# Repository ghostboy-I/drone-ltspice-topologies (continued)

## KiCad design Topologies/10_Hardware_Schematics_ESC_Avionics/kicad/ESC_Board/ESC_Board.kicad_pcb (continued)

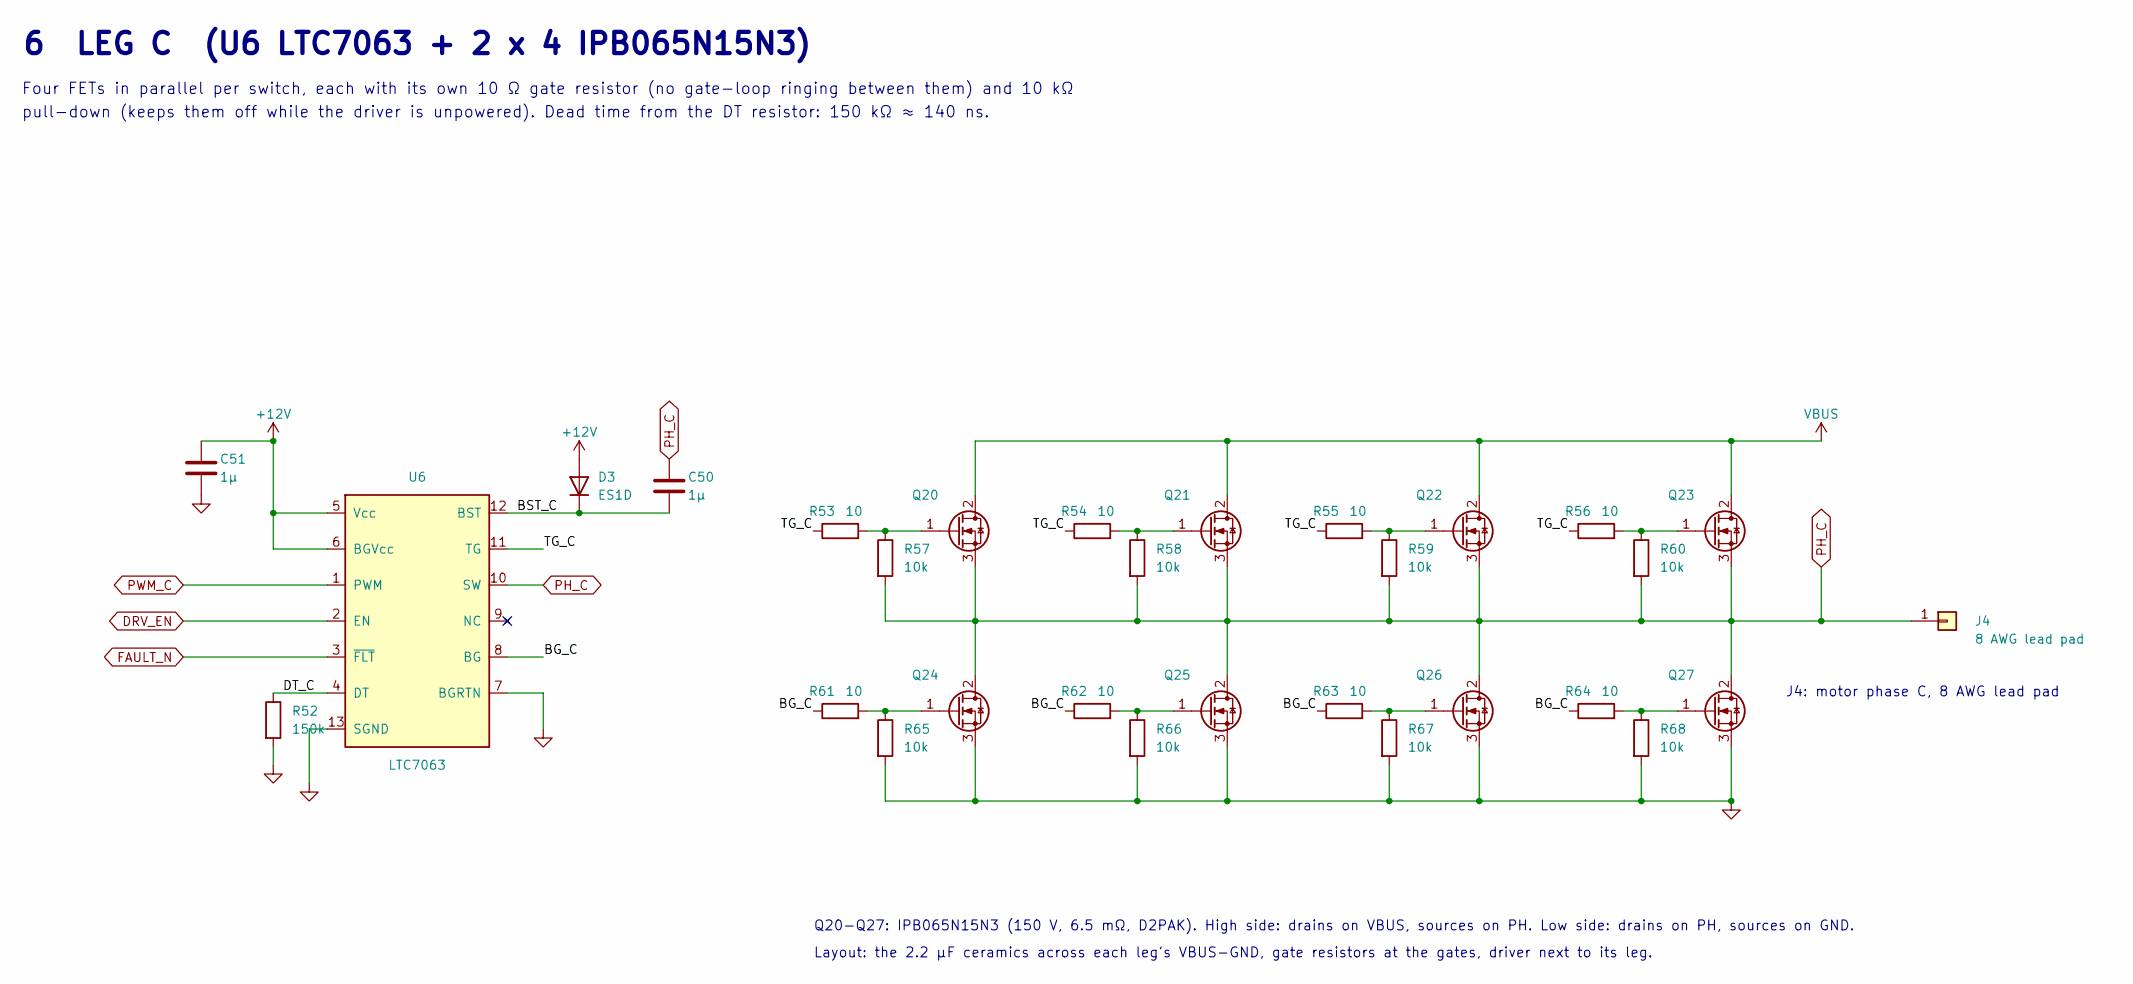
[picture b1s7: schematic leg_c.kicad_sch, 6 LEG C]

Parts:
C50, C51: 1µ; C_0805_2012Metric; Rating 25 V; MPN/Spec X7R
D3: ES1D; D_SMA; Rating 200 V 1 A; MPN/Spec ES1D
J4: 8 AWG lead pad; SolderWire-8AWG_1x01_D4.2mm_OD7mm; MPN/Spec 8 AWG lead pad (8 mm bullet on the lead)
Q20, Q21, Q22, Q23, Q24, Q25, Q26, Q27: IPB065N15N3; TO-263-2; Rating 150 V 130 A; MPN/Spec Infineon IPB065N15N3 G
R52: 150k; R_0603_1608Metric; MPN/Spec 1 %, thick film
R53, R54, R55, R56, R61, R62, R63, R64: 10; R_0603_1608Metric; MPN/Spec 1 %
R57, R58, R59, R60, R65, R66, R67, R68: 10k; R_0603_1608Metric; MPN/Spec 1 %
U6: LTC7063; MSOP-12-1EP_3x4.039mm_P0.65mm_EP1.651x2.845mm; Rating 150 V; MPN/Spec LTC7063EMSE (MSOP-12)

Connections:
+12V: C51.1, D3.2 (A), U6.5 (Vcc), U6.6 (BGVcc); also elsewhere on the board
/Leg_C/BG_C: R61.1, R62.1, R63.1, R64.1, U6.8 (BG)
/Leg_C/BST_C: C50.1, D3.1 (K), U6.12 (BST)
/Leg_C/DT_C: R52.1, U6.4 (DT)
/Leg_C/TG_C: R53.1, R54.1, R55.1, R56.1, U6.11 (TG)
DRV_EN: U6.2 (EN); also elsewhere on the board
FAULT_N: U6.3 (~FLT); also elsewhere on the board
GND: C51.2, Q24.3 (S), Q25.3 (S), Q26.3 (S), Q27.3 (S), R52.2, R65.2, R66.2, R67.2, R68.2, U6.7 (BGRTN), U6.13 (SGND); also elsewhere on the board
unnamed: Q20.1 (G), R53.2, R57.1
unnamed: Q21.1 (G), R54.2, R58.1
unnamed: Q22.1 (G), R55.2, R59.1
unnamed: Q23.1 (G), R56.2, R60.1
unnamed: Q24.1 (G), R61.2, R65.1
unnamed: Q25.1 (G), R62.2, R66.1
unnamed: Q26.1 (G), R63.2, R67.1
unnamed: Q27.1 (G), R64.2, R68.1
PH_C: C50.2, J4.1, Q20.3 (S), Q21.3 (S), Q22.3 (S), Q23.3 (S), Q24.2 (D), Q25.2 (D), Q26.2 (D), Q27.2 (D), R57.2, R58.2, R59.2, R60.2, U6.10 (SW)
PWM_C: U6.1 (PWM); also elsewhere on the board
VBUS: Q20.2 (D), Q21.2 (D), Q22.2 (D), Q23.2 (D); also elsewhere on the board

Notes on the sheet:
6 LEG C (U6 LTC7063 + 2 x 4 IPB065N15N3)
Four FETs in parallel per switch, each with its own 10 Ω gate resistor (no gate-loop ringing between them) and 10 kΩ
pull-down (keeps them off while the driver is unpowered). Dead time from the DT resistor: 150 kΩ ≈ 140 ns.
J4: motor phase C, 8 AWG lead pad
Q20-Q27: IPB065N15N3 (150 V, 6.5 mΩ, D2PAK). High side: drains on VBUS, sources on PH. Low side: drains on PH, sources on GND.
Layout: the 2.2 µF ceramics across each leg's VBUS-GND, gate resistors at the gates, driver next to its leg.

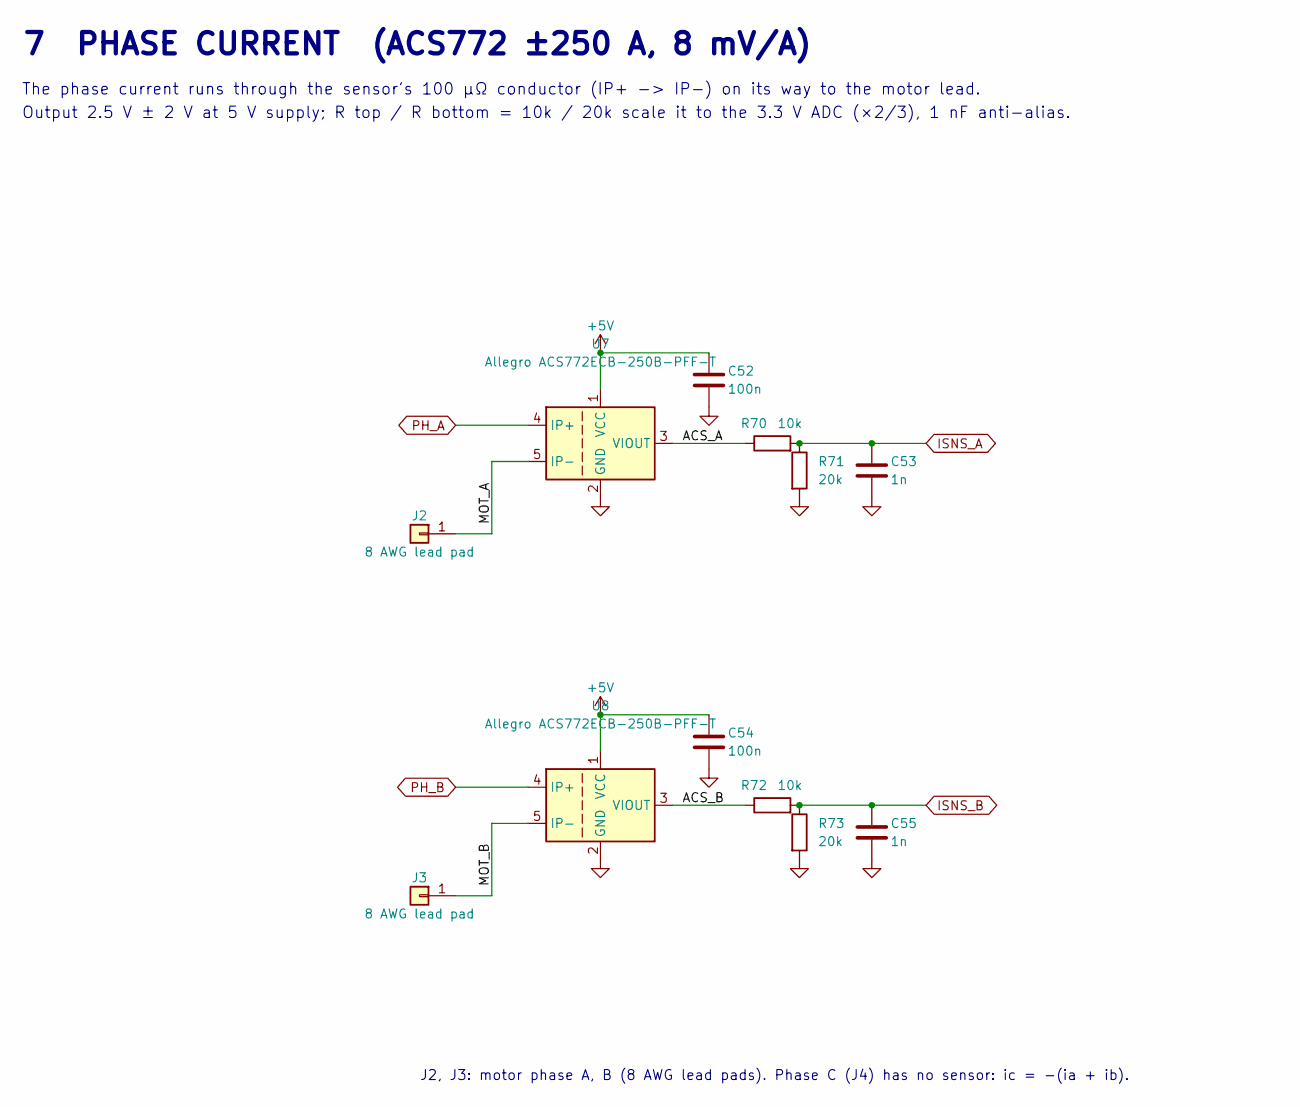
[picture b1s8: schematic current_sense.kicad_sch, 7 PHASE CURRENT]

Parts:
C52, C54: 100n; C_0603_1608Metric; MPN/Spec X7R
C53, C55: 1n; C_0603_1608Metric; MPN/Spec X7R
J2, J3: 8 AWG lead pad; SolderWire-8AWG_1x01_D4.2mm_OD7mm; MPN/Spec 8 AWG lead pad (8 mm bullet on the lead)
R70, R72: 10k; R_0603_1608Metric; MPN/Spec 1 %, thick film
R71, R73: 20k; R_0603_1608Metric; MPN/Spec 1 %, thick film
U7, U8: Allegro ACS772ECB-250B-PFF-T; Allegro_CB_PFF; Rating ±250 A; MPN/Spec Allegro ACS772ECB-250B-PFF-T

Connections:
+5V: C52.1, C54.1, U7.1 (VCC), U8.1 (VCC); also elsewhere on the board
/Current_Sense/ACS_A: R70.1, U7.3 (VIOUT)
/Current_Sense/ACS_B: R72.1, U8.3 (VIOUT)
/Current_Sense/MOT_A: J2.1, U7.5 (IP-)
/Current_Sense/MOT_B: J3.1, U8.5 (IP-)
GND: C52.2, C53.2, C54.2, C55.2, R71.2, R73.2, U7.2 (GND), U8.2 (GND); also elsewhere on the board
ISNS_A: C53.1, R70.2, R71.1; also elsewhere on the board
ISNS_B: C55.1, R72.2, R73.1; also elsewhere on the board
PH_A: U7.4 (IP+); also elsewhere on the board
PH_B: U8.4 (IP+); also elsewhere on the board

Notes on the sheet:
7 PHASE CURRENT (ACS772 ±250 A, 8 mV/A)
The phase current runs through the sensor's 100 µΩ conductor (IP+ -> IP-) on its way to the motor lead.
Output 2.5 V ± 2 V at 5 V supply; R top / R bottom = 10k / 20k scale it to the 3.3 V ADC (×2/3), 1 nF anti-alias.
J2, J3: motor phase A, B (8 AWG lead pads). Phase C (J4) has no sensor: ic = -(ia + ib).

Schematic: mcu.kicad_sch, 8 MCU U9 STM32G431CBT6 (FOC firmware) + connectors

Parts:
C56, C57, C58, C59, C62, C63: 100n; C_0603_1608Metric; MPN/Spec X7R
C60: 4.7µ; C_0805_2012Metric; Rating 10 V; MPN/Spec X7R
C61: 1µ; C_0603_1608Metric; MPN/Spec X7R
D4: QTLP690C; LED_0603_1608Metric; MPN/Spec any 0603 green LED
FB1: 600R@100MHz; L_0603_1608Metric; MPN/Spec Murata BLM18PG601SN1
J5: GH 3 pin; JST_GH_BM03B-GHS-TBT_1x03-1MP_P1.25mm_Vertical; MPN/Spec JST GH 3 pin
J6: GH 6 pin; JST_GH_BM06B-GHS-TBT_1x06-1MP_P1.25mm_Vertical; MPN/Spec JST GH 6 pin
J7: Tag-Connect TC2030-NL; Tag-Connect_TC2030-IDC-NL_2x03_P1.27mm_Vertical; MPN/Spec Tag-Connect TC2030-NL
R69, R74: 10k; R_0603_1608Metric; MPN/Spec 1 %, thick film
R75: 1k; R_0603_1608Metric; MPN/Spec 1 %, thick film
R76: 100; R_0603_1608Metric; MPN/Spec 1 %, thick film
U9: ST STM32G431CBT6; LQFP-48_7x7mm_P0.5mm; MPN/Spec ST STM32G431CBT6 (LQFP-48)

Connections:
+3V3: C56.1, C57.1, C58.1, C59.1, C60.1, D4.2 (A), FB1.1, J7.1, R69.1, U9.1 (VBAT), U9.24 (VDD), U9.36 (VDD), U9.48 (VDD); also elsewhere on the board
+5V: J6.1; also elsewhere on the board
/MCU/BOOT0: R74.1, U9.45 (PB8)
/MCU/ENC_CS: J6.3, U9.12 (PA4)
/MCU/ENC_MISO: J6.5, U9.14 (PA6)
/MCU/ENC_MOSI: J6.6, U9.15 (PA7)
/MCU/ENC_SCK: J6.4, U9.13 (PA5)
/MCU/LED: R75.1, U9.2 (PC13)
/MCU/NRST: C63.1, J7.3, U9.7 (PG10)
/MCU/SIG_IN: R76.2, U9.39 (PA15)
/MCU/SWCLK: J7.4, U9.38 (PA14)
/MCU/SWDIO: J7.2, U9.37 (PA13)
/MCU/TLM_TX: J5.2, U9.43 (PB6)
DRV_EN: U9.16 (PB0); also elsewhere on the board
FAULT_N: R69.2, U9.26 (PB12); also elsewhere on the board
GND: C56.2, C57.2, C58.2, C59.2, C60.2, C61.2, C62.2, C63.2, J5.3, J6.2, J7.5, R74.2, U9.19 (VSSA), U9.23 (VSS), U9.35 (VSS), U9.47 (VSS); also elsewhere on the board
ISNS_A: U9.8 (PA0); also elsewhere on the board
ISNS_B: U9.9 (PA1); also elsewhere on the board
unnamed: D4.1 (K), R75.2
unnamed: J5.1, R76.1
PWM_A: U9.30 (PA8); also elsewhere on the board
PWM_B: U9.31 (PA9); also elsewhere on the board
PWM_C: U9.32 (PA10); also elsewhere on the board
TEMP: U9.11 (PA3); also elsewhere on the board
VBUS_SNS: U9.10 (PA2); also elsewhere on the board
VDDA: C61.1, C62.1, FB1.2, U9.20 (VREF+), U9.21 (VDDA)

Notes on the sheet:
8 MCU (U9 STM32G431CBT6, Cortex-M4F 170 MHz)
TIM1 CH1-3 (PA8-PA10) drive the three legs; ADC on PA0-PA3; SPI1 (PA4-PA7) reads the AS5047P encoder;
PA15 takes DShot from the flight controller, PB6 sends telemetry. The pin map is a proposal: check it in STM32CubeMX.
C56-C59 100 nF at the four VDD/VBAT pins, C60 4.7 µF
VDDA / VREF+: ferrite bead + 1 µF + 100 nF
R69: pull-up for the three drivers' open-drain FLT outputs (wired-OR)
J5: DShot in (R76 100 Ω series), telemetry out, GND (JST GH 3)
J6: AS5047P encoder on the motor, SPI (JST GH 6)
J7: Tag-Connect TC2030-NL (SWD); pad 6 SWO unused

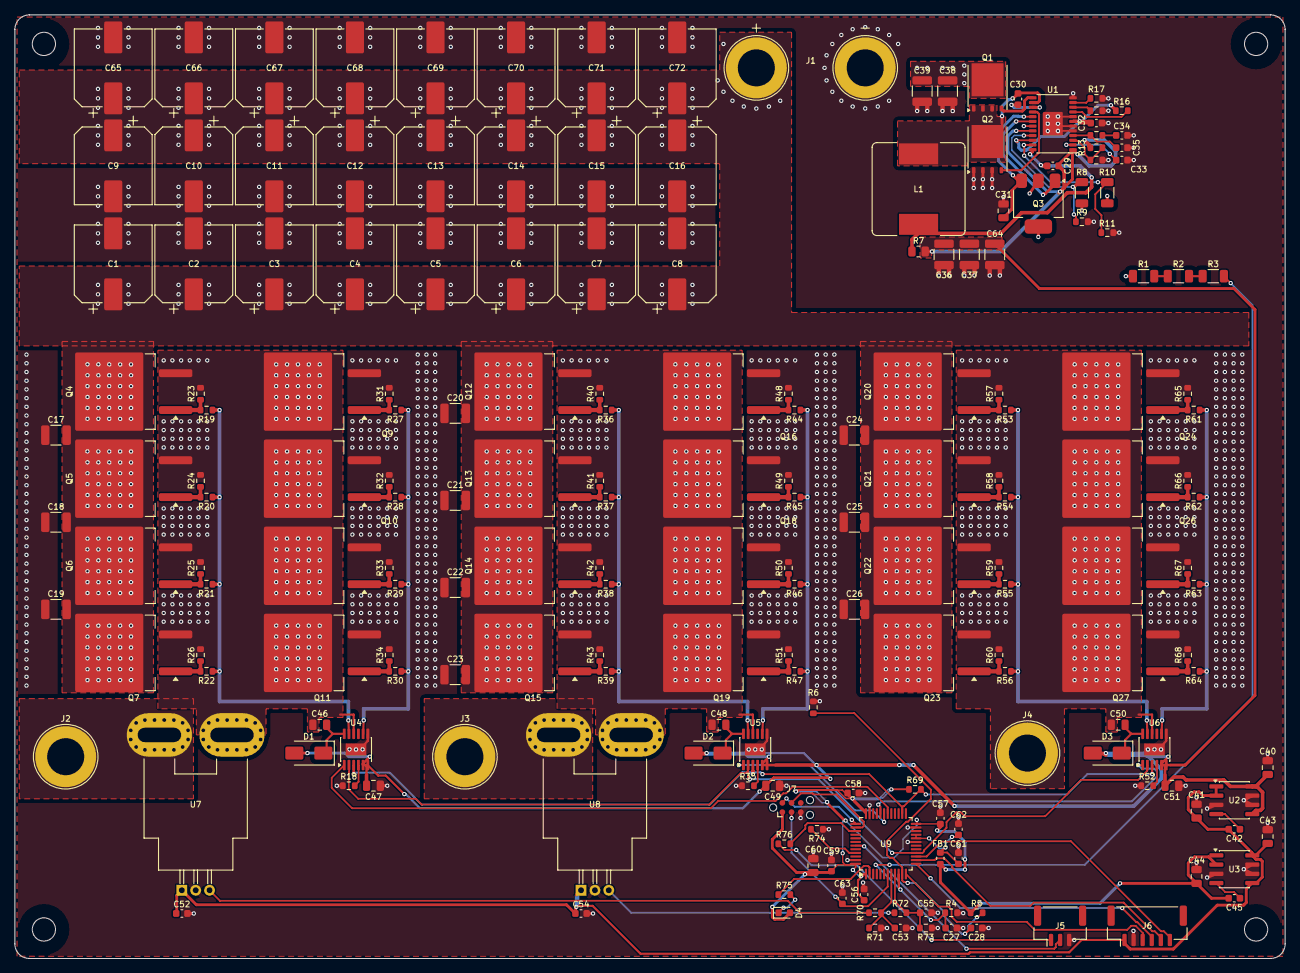
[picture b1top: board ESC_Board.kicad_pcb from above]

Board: 4 copper layers, 175.0 x 130.0 mm, 201 parts (0 on the bottom side), 92 nets.

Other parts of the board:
H1, H2, H3, H4: M3; MountingHole_3.2mm_M3

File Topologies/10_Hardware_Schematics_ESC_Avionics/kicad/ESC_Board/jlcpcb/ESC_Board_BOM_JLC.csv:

Comment,Designator,Footprint,LCSC Part #
"150u 150 uF 125 V hybrid polymer, >=3.5 A ripple, ESR <= 20 mR 125 V","C1,C2,C3,C4,C5,C6,C7,C8,C9,C10,C11,C12,C13,C14,C15,C16,C65,C66,C67,C68,C69,C70,C71,C72",CP_Elec_10x12.5,
2.2u 2.2 uF X7R 1210 (~1.1 uF at 90 V) 250 V,"C17,C18,C19,C20,C21,C22,C23,C24,C25,C26,C38,C39",C_1210_3225Metric,
10n X7R,"C27,C33",C_0603_1608Metric,
100n X7R,"C28,C52,C54,C56,C57,C58,C59,C62,C63",C_0603_1608Metric,
1n X7R,"C29,C53,C55",C_0603_1608Metric,
0.1u X7R 25 V,C30,C_0603_1608Metric,
4.7u X7R 25 V,C31,C_0805_2012Metric,
0.1u X7R,C32,C_0603_1608Metric,
1.8n X7R,C34,C_0603_1608Metric,
18p X7R,C35,C_0603_1608Metric,
10u 10 uF X7R 1210 (5 uF at 12 V) 25 V,"C36,C37",C_1210_3225Metric,
1u X7R 25 V,"C40,C46,C47,C48,C49,C50,C51",C_0805_2012Metric,
10u X7R 10 V,"C41,C44",C_0805_2012Metric,
"10 nF X7R 10 nF X7R, DNP","C42,C45",C_0603_1608Metric,
1u X7R 10 V,C43,C_0805_2012Metric,
4.7u X7R 10 V,C60,C_0805_2012Metric,
1u X7R,C61,C_0603_1608Metric,
47u 47 uF X7R 1210 (~22 uF at 12 V) 25 V,C64,C_1210_3225Metric,
ES1D ES1D 200 V 1 A,"D1,D2,D3",D_SMA,
QTLP690C any 0603 green LED,D4,LED_0603_1608Metric,
600R@100MHz Murata BLM18PG601SN1,FB1,L_0603_1608Metric,
"AS150 with factory 8 AWG pigtail AMASS AS150 with factory 8 AWG pigtail (male) 150 A, 24S",J1,AMASS_AS150_Pigtail_2x8AWG_P15mm,
8 AWG lead pad 8 AWG lead pad (8 mm bullet on the lead),"J2,J3,J4",SolderWire-8AWG_1x01_D4.2mm_OD7mm,
GH 3 pin JST GH 3 pin,J5,JST_GH_BM03B-GHS-TBT_1x03-1MP_P1.25mm_Vertical,
GH 6 pin JST GH 6 pin,J6,JST_GH_BM06B-GHS-TBT_1x06-1MP_P1.25mm_Vertical,
Tag-Connect TC2030-NL Tag-Connect TC2030-NL,J7,Tag-Connect_TC2030-IDC-NL_2x03_P1.27mm_Vertical,
"150u shielded, Isat >= 1 A, DCR <= 0.4 R Isat 1 A",L1,L_Bourns_SRR1260,
BSC520N15NS3 Infineon BSC520N15NS3 150 V 21 A,Q1,TDSON-8-1,
BSC360N15NS3 Infineon BSC360N15NS3 150 V 30 A,Q2,TDSON-8-1,
BSP89 Infineon BSP89 240 V,Q3,SOT-223-3_TabPin2,
IPB065N15N3 Infineon IPB065N15N3 G 150 V 130 A,"Q4,Q5,Q6,Q7,Q8,Q9,Q10,Q11,Q12,Q13,Q14,Q15,Q16,Q17,Q18,Q19,Q20,Q21,Q22,Q23,Q24,Q25,Q26,Q27",TO-263-2,
"330k 1 %, thick film 200 V","R1,R2,R3",R_1206_3216Metric,
"33k 1 %, thick film",R4,R_0603_1608Metric,
"10k 1 %, thick film","R5,R14,R69,R70,R72,R74",R_0603_1608Metric,
10k NTC 10 kR B3950,R6,R_0603_1608Metric,
100m current sense 1 % 0.25 W,R7,R_0805_2012Metric,
"976k 1 %, thick film 200 V",R8,R_1206_3216Metric,
"20k 1 %, thick film","R9,R71,R73",R_0603_1608Metric,
"1Meg 1 %, thick film 200 V",R10,R_1206_3216Metric,
"10.2k 1 %, thick film",R11,R_0603_1608Metric,
"64.9k 1 %, thick film",R12,R_0603_1608Metric,
"140k 1 %, thick film",R13,R_0603_1608Metric,
"36.5k 1 %, thick film",R15,R_0603_1608Metric,
"100k 1 %, thick film","R16,R17",R_0603_1608Metric,
"150k 1 %, thick film","R18,R35,R52",R_0603_1608Metric,
10 1 %,"R19,R20,R21,R22,R27,R28,R29,R30,R36,R37,R38,R39,R44,R45,R46,R47,R53,R54,R55,R56,R61,R62,R63,R64",R_0603_1608Metric,
10k 1 %,"R23,R24,R25,R26,R31,R32,R33,R34,R40,R41,R42,R43,R48,R49,R50,R51,R57,R58,R59,R60,R65,R66,R67,R68",R_0603_1608Metric,
"1k 1 %, thick film",R75,R_0603_1608Metric,
"100 1 %, thick film",R76,R_0603_1608Metric,
LTC7801 LTC7801EFE (TSSOP-24 with exposed pad) 150 V,U1,Linear_HTSSOP-24-1EP_4.4x7.8mm_P0.65mm_EP2.74x3.25mm,
LT1763-5 LT1763CS8-5 (SO-8) 20 V,U2,SOIC-8_3.9x4.9mm_P1.27mm,
LT1763-3.3 LT1763CS8-3.3 (SO-8) 20 V,U3,SOIC-8_3.9x4.9mm_P1.27mm,
LTC7063 LTC7063EMSE (MSOP-12) 150 V,"U4,U5,U6",MSOP-12-1EP_3x4.039mm_P0.65mm_EP1.651x2.845mm,
Allegro ACS772ECB-250B-PFF-T Allegro ACS772ECB-250B-PFF-T ±250 A,"U7,U8",Allegro_CB_PFF,
ST STM32G431CBT6 ST STM32G431CBT6 (LQFP-48),U9,LQFP-48_7x7mm_P0.5mm,

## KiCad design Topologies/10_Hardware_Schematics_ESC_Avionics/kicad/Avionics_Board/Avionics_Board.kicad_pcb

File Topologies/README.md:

# Drone Motor Power Topologies (LTspice)

| # | Topology | Folder | Status |
|---|---|---|---|
| 01 | Half-bridge (synchronous buck / one ESC leg) → DC motor equivalent | `01_Half-Bridge_Motor_Drive/` | Done, verified by simulation |
| 02 | 3-phase inverter (ESC) + BLDC, 6-step trapezoidal commutation, Hall-sensored | `02_Three-Phase_ESC_BLDC_6-Step/` | Done, verified by simulation |
| 03 | 3-phase inverter + PMSM, sensored field-oriented control (FOC) with SVPWM | `03_Three-Phase_FOC_PMSM/` | Done, verified by simulation |
| 04 | Three-channel power transmission: 3 batteries → 3 harnesses → 3 ESCs, independent (plug-in, ripple, resonance, grounding) | `04_Three-Channel_Power_Transmission/` | Done, verified by simulation |
| 05 | Per-channel protection: back-to-back MOSFET soft-start (anti-spark) + reverse-polarity block, vs XT60 / XT90-S | `05_Channel_Protection_Soft-Start_Reverse-Polarity/` | Done, verified by simulation |
| 06 | BEC: synchronous buck 4S → 5 V / 3 A for avionics (voltage mode, Type III, input feed-forward) | `06_BEC_Synchronous_Buck_5V/` | Done, verified by simulation |
| 07 | Full 3-battery → 3-motor system: three protected channels, three switching FOC ESCs on their own harnesses, plus the BEC (plug-in/arming, flight, punch, pack loss) | `07_Three-Channel_Full_System/` | Done, verified by simulation |
| 08 | Redundant avionics power: feed the BEC from all three packs (ideal-diode OR-ing) without creating ground loops | `08_Redundant_Avionics_Power/` | Done, verified by simulation |
| 09 | 24S channel of the real tricopter: FOC drive (03) on a U15XL with bootstrap gate drive, ESC 12 V + 3.3 V supply, avionics 12 V (transmitter) → 5 V (06, controller + receiver) → 3.3 V | `09_24S_FOC_Drive_Low-Voltage_Rails/` | Done, verified by simulation |
| 10 | Hardware schematics of 09 with real parts: ESC board (LTC7801 aux, 3 × LTC7063, 24 × IPB065N15N3, ACS772, STM32G431) and avionics power board (diode-OR, LTC4366 surge stopper, LTC7801, LT8641, LT3045), with BOMs and KiCad 9 projects for both boards: drawn schematics, every footprint in one project library, and both PCBs laid out, routed and DRC-clean with JLCPCB files (avionics 100 × 62 mm; ESC 175 × 130 mm, 4 layers, 2 oz, bus bars) | `10_Hardware_Schematics_ESC_Avionics/` | Done, verified by simulation |
| 11 | Whole power system drawn part by part: 3 packs → 3 drawn ESC boards (every FET, driver, sensor, MCU) → 3 U15XL motors, plus the drawn avionics board, in one LTspice run; KiCad entry guide | `11_Whole_System_Schematic/` | Done, verified by simulation |
| 12 | Full H-bridge (bidirectional / reversing) | — | Optional |

**Flow chart of the whole system with part numbers:** [`System_Flowchart/System_Flowchart.pdf`](System_Flowchart/README.md), every block tagged with the topologies that cover it.

**Parts alternatives study:** [`Alternatives_Study/Alternatives_Study.pdf`](Alternatives_Study/README.md), alternative parts and methods for every section of the two boards, judged at the 24S hover and punch points.

**End goal:** three batteries driving three motors independently. Transmission (04, 05), down-conversion for avionics (06), then the full system (07), redundant avionics power (08), and the move to the real 24S packs with every low-voltage rail (09).

`tools/ltraw.py` reads LTspice binary `.raw` files into Python so results can be plotted.

`tools/sweep.py` runs parameter sweeps in parallel: one LTspice process per case, several at once, results in
`<topology>/sweeps/<name>/results.csv`. Example (from this folder):
```bash
python3 tools/sweep.py 02_Three-Phase_ESC_BLDC_6-Step/ThreePhase_ESC_BLDC.asc --param Duty=0.3,0.5,0.7,0.9 --param Sync=0,1 --name duty
```
A single transient run cannot be split across cores (every time step needs the one before it), but separate cases are
independent, so a sweep scales with core count. Each ESC run keeps about 2 cores busy and uses ~0.17 GB, so the default
is one job per 2 cores (`--jobs` overrides). Topology 02 has a worked example: `sweep_fsw.py`.

Each topology folder has its schematic, a README, results plot and `NN_<Topology>_Design.pdf` (the math). Rebuild that PDF with `make_design_doc.py`.

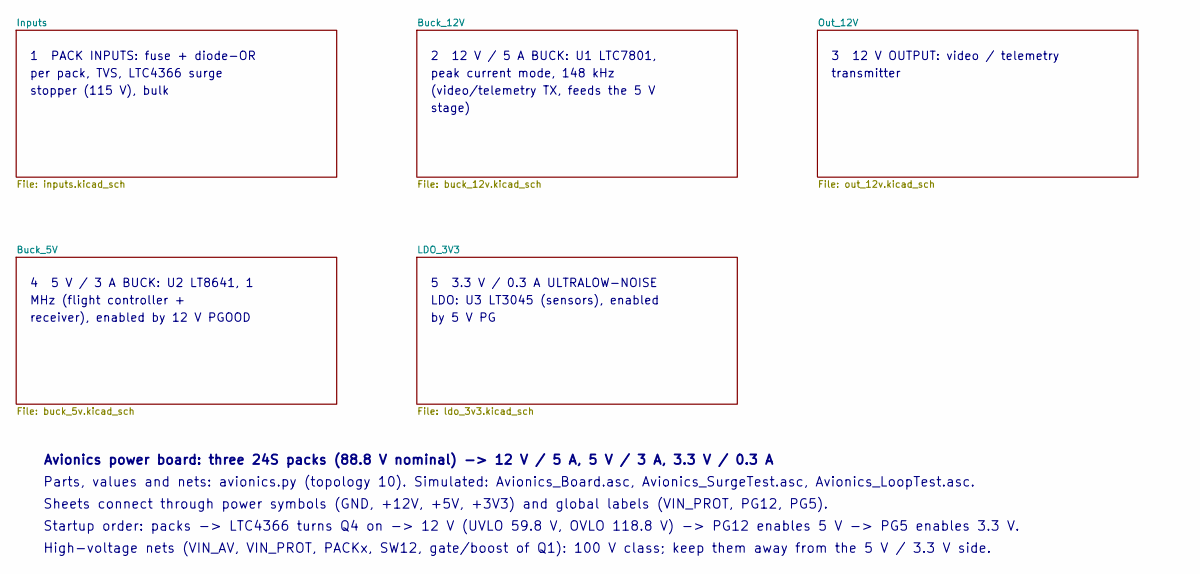
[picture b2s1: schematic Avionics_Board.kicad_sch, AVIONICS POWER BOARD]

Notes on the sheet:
1 PACK INPUTS: fuse + diode-OR
per pack, TVS, LTC4366 surge
stopper (115 V), bulk
2 12 V / 5 A BUCK: U1 LTC7801,
peak current mode, 148 kHz
(video/telemetry TX, feeds the 5 V
stage)
3 12 V OUTPUT: video / telemetry
transmitter
4 5 V / 3 A BUCK: U2 LT8641, 1
MHz (flight controller +
receiver), enabled by 12 V PGOOD
5 3.3 V / 0.3 A ULTRALOW-NOISE
LDO: U3 LT3045 (sensors), enabled
by 5 V PG
Avionics power board: three 24S packs (88.8 V nominal) -> 12 V / 5 A, 5 V / 3 A, 3.3 V / 0.3 A
Parts, values and nets: avionics.py (topology 10). Simulated: Avionics_Board.asc, Avionics_SurgeTest.asc, Avionics_LoopTest.asc.
Sheets connect through power symbols (GND, +12V, +5V, +3V3) and global labels (VIN_PROT, PG12, PG5).
Startup order: packs -> LTC4366 turns Q4 on -> 12 V (UVLO 59.8 V, OVLO 118.8 V) -> PG12 enables 5 V -> PG5 enables 3.3 V.
High-voltage nets (VIN_AV, VIN_PROT, PACKx, SW12, gate/boost of Q1): 100 V class; keep them away from the 5 V / 3.3 V side.

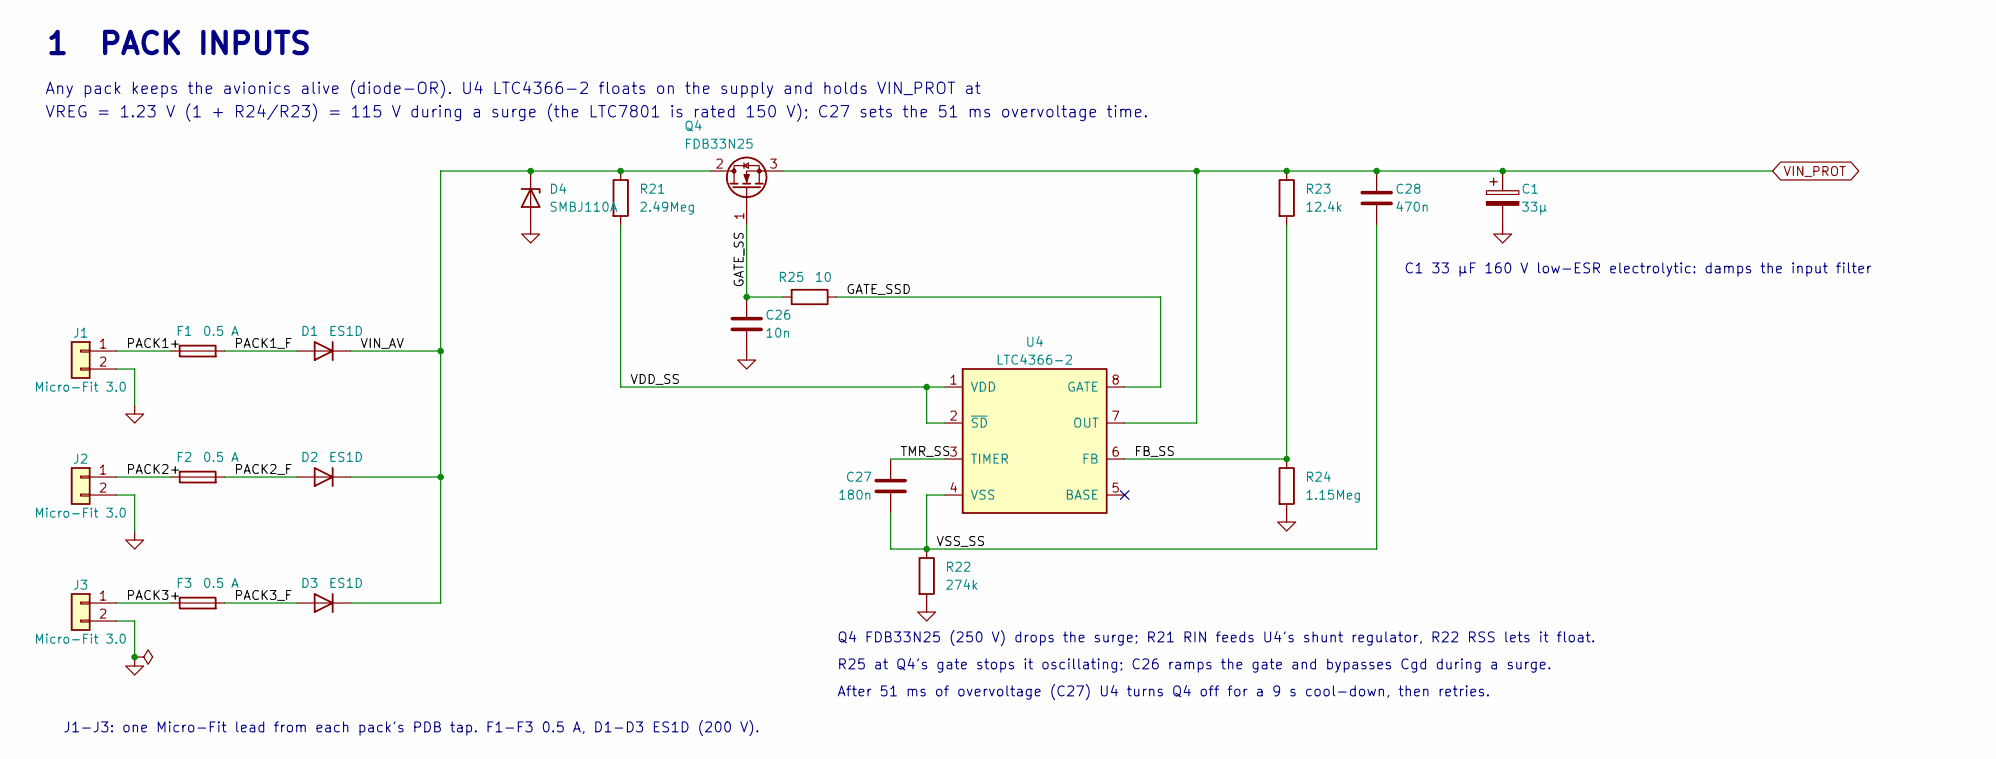
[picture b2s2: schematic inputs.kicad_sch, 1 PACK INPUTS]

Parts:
C1: 33µ; CP_Radial_D10.0mm_P5.00mm; Rating 160 V; MPN/Spec Aluminium electrolytic, low ESR
C26: 10n; C_1206_3216Metric; Rating 250 V; MPN/Spec X7R 1206 250 V (e.g. Murata GRM31BR72E1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
C27: 180n; C_0603_1608Metric; MPN/Spec X7R
C28: 470n; C_0805_2012Metric; Rating 25 V; MPN/Spec X7R
D1, D2, D3: ES1D; D_SMA; Rating 200 V 1 A; MPN/Spec ES1D
D4: SMBJ110A; D_SMB; Rating VBR 122 V; MPN/Spec SMBJ110A
F1, F2, F3: 0.5 A; Fuse_1206_3216Metric; Rating 125 V DC; MPN/Spec Littelfuse 0451.500 (NANO2, 125 V DC)
J1, J2, J3: Micro-Fit 3.0; Molex_Micro-Fit_3.0_43650-0215_1x02_P3.00mm_Vertical; Rating ≥150 V; MPN/Spec Molex Micro-Fit 3.0, 2 pin (600 V, 5 A)
Q4: FDB33N25; TO-263-2; Rating 250 V 33 A; MPN/Spec onsemi FDB33N25 (250 V, 94 mΩ, D2PAK)
R21: 2.49Meg; R_1206_3216Metric; Rating 200 V; MPN/Spec 1 %, thick film
R22: 274k; R_1206_3216Metric; Rating 200 V; MPN/Spec 1 %, thick film
R23: 12.4k; R_0603_1608Metric; MPN/Spec 1 %, thick film
R24: 1.15Meg; R_1206_3216Metric; Rating 200 V; MPN/Spec 1 %, thick film
R25: 10; R_0603_1608Metric; MPN/Spec 1 %, thick film
U4: LTC4366-2; TSOT-23-8; Rating 9 V to >500 V (floating); MPN/Spec LTC4366CTS8-2 (TSOT-23-8)

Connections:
/Inputs/FB_SS: R23.2, R24.1, U4.6 (FB)
/Inputs/GATE_SS: C26.1, Q4.1 (G), R25.2
/Inputs/GATE_SSD: R25.1, U4.8 (GATE)
/Inputs/PACK1+: F1.1, J1.1
/Inputs/PACK1_F: D1.2 (A), F1.2
/Inputs/PACK2+: F2.1, J2.1
/Inputs/PACK2_F: D2.2 (A), F2.2
/Inputs/PACK3+: F3.1, J3.1
/Inputs/PACK3_F: D3.2 (A), F3.2
/Inputs/TMR_SS: C27.1, U4.3 (TIMER)
/Inputs/VDD_SS: R21.2, U4.1 (VDD), U4.2 (~SD)
/Inputs/VIN_AV: D1.1 (K), D2.1 (K), D3.1 (K), D4.1 (K), Q4.2 (D), R21.1
/Inputs/VSS_SS: C27.2, C28.2, R22.1, U4.4 (VSS)
GND: C1.2, C26.2, D4.2 (A), J1.2, J2.2, J3.2, R22.2, R24.2; also elsewhere on the board
VIN_PROT: C1.1, C28.1, Q4.3 (S), R23.1, U4.7 (OUT); also elsewhere on the board

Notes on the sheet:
1 PACK INPUTS
Any pack keeps the avionics alive (diode-OR). U4 LTC4366-2 floats on the supply and holds VIN_PROT at
VREG = 1.23 V (1 + R24/R23) = 115 V during a surge (the LTC7801 is rated 150 V); C27 sets the 51 ms overvoltage time.
J1-J3: one Micro-Fit lead from each pack's PDB tap. F1-F3 0.5 A, D1-D3 ES1D (200 V).
Q4 FDB33N25 (250 V) drops the surge; R21 RIN feeds U4's shunt regulator, R22 RSS lets it float.
R25 at Q4's gate stops it oscillating; C26 ramps the gate and bypasses Cgd during a surge.
After 51 ms of overvoltage (C27) U4 turns Q4 off for a 9 s cool-down, then retries.
C1 33 µF 160 V low-ESR electrolytic: damps the input filter

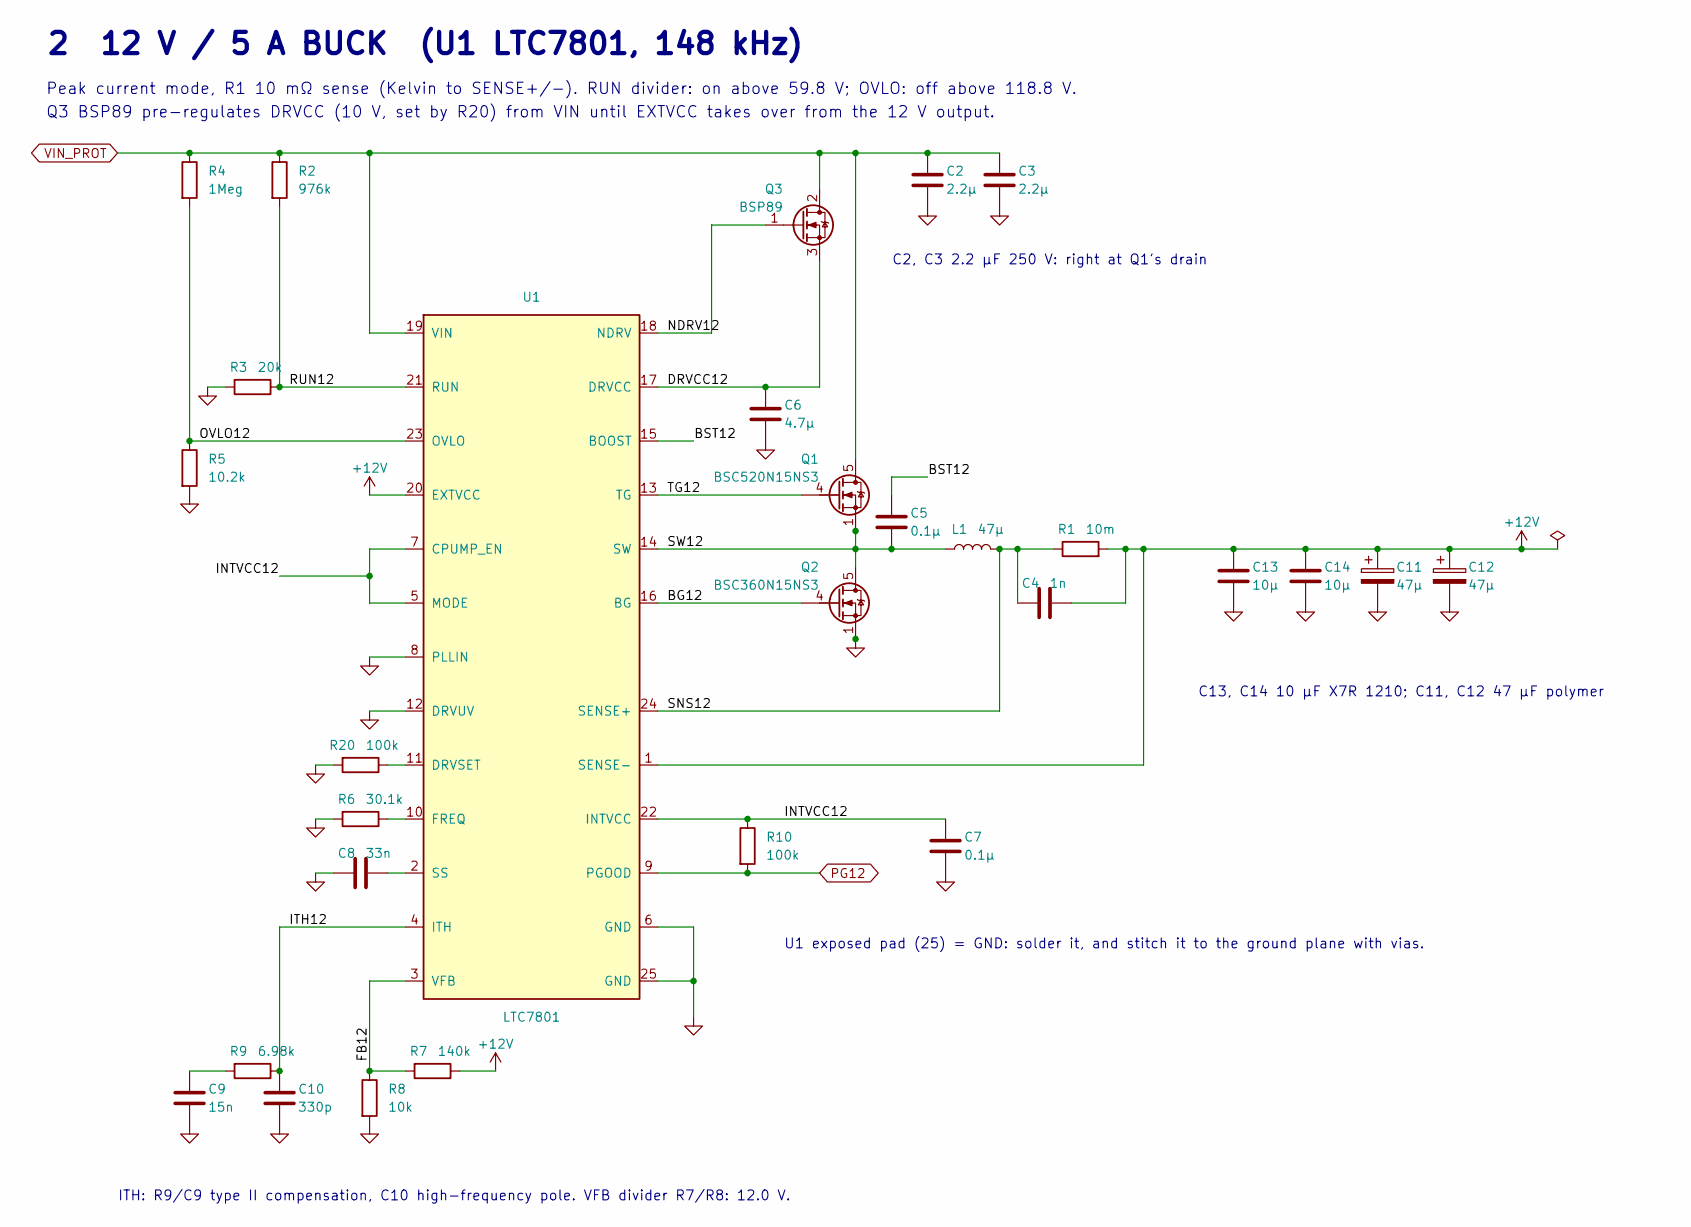
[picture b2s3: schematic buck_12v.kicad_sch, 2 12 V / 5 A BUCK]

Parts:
C2, C3: 2.2µ; C_1210_3225Metric; Rating 250 V; MPN/Spec X7R 1210
C4: 1n; C_0603_1608Metric; MPN/Spec X7R
C5: 0.1µ; C_0603_1608Metric; Rating 25 V; MPN/Spec X7R
C6: 4.7µ; C_0805_2012Metric; Rating 25 V; MPN/Spec X7R
C7: 0.1µ; C_0603_1608Metric; MPN/Spec X7R
C8: 33n; C_0603_1608Metric; MPN/Spec X7R
C9: 15n; C_0603_1608Metric; MPN/Spec X7R
C10: 330p; C_0603_1608Metric; MPN/Spec X7R
C11, C12: 47µ; CP_Elec_6.3x7.7; Rating 25 V; MPN/Spec Polymer, ESR ≤ 15 mΩ
C13, C14: 10µ; C_1210_3225Metric; Rating 25 V; MPN/Spec 10 µF X7R 1210 (5 µF at 12 V bias)
L1: 47µ; L_Coilcraft_XAL1010-XXX; Rating Isat 9.2 A; MPN/Spec shielded 10x10 mm (e.g. Coilcraft XAL10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
Q1: BSC520N15NS3; TDSON-8-1; Rating 150 V 21 A; MPN/Spec Infineon BSC520N15NS3
Q2: BSC360N15NS3; TDSON-8-1; Rating 150 V 30 A; MPN/Spec Infineon BSC360N15NS3
Q3: BSP89; SOT-223-3_TabPin2; Rating 240 V; MPN/Spec Infineon BSP89
R1: 10m; R_2512_6332Metric; Rating 1 W; MPN/Spec current sense, 1 %, 1 W
R2: 976k; R_1206_3216Metric; Rating 200 V; MPN/Spec 1 %, thick film
R3: 20k; R_0603_1608Metric; MPN/Spec 1 %, thick film
R4: 1Meg; R_1206_3216Metric; Rating 200 V; MPN/Spec 1 %, thick film
R5: 10.2k; R_0603_1608Metric; MPN/Spec 1 %, thick film
R6: 30.1k; R_0603_1608Metric; MPN/Spec 1 %, thick film
R7: 140k; R_0603_1608Metric; MPN/Spec 1 %, thick film
R8: 10k; R_0603_1608Metric; MPN/Spec 1 %, thick film
R9: 6.98k; R_0603_1608Metric; MPN/Spec 1 %, thick film
R10, R20: 100k; R_0603_1608Metric; MPN/Spec 1 %, thick film
U1: LTC7801; Linear_HTSSOP-24-1EP_4.4x7.8mm_P0.65mm_EP2.74x3.25mm; Rating 150 V; MPN/Spec LTC7801EFE (TSSOP-24 with exposed pad)

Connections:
+12V: C4.2, C11.1, C12.1, C13.1, C14.1, R1.2, R7.1, U1.1 (SENSE-), U1.20 (EXTVCC); also elsewhere on the board
/Buck_12V/BG12: Q2.4 (G), U1.16 (BG)
/Buck_12V/BST12: C5.1, U1.15 (BOOST)
/Buck_12V/DRVCC12: C6.1, Q3.3 (S), U1.17 (DRVCC)
/Buck_12V/FB12: R7.2, R8.1, U1.3 (VFB)
/Buck_12V/INTVCC12: C7.1, R10.1, U1.5 (MODE), U1.7 (CPUMP_EN), U1.22 (INTVCC)
/Buck_12V/ITH12: C10.1, R9.1, U1.4 (ITH)
/Buck_12V/NDRV12: Q3.1 (G), U1.18 (NDRV)
/Buck_12V/OVLO12: R4.2, R5.1, U1.23 (OVLO)
/Buck_12V/RUN12: R2.2, R3.1, U1.21 (RUN)
/Buck_12V/SNS12: C4.1, L1.2, R1.1, U1.24 (SENSE+)
/Buck_12V/SW12: C5.2, L1.1, Q1.1 (S), Q1.2 (S), Q1.3 (S), Q2.5 (D), U1.14 (SW)
/Buck_12V/TG12: Q1.4 (G), U1.13 (TG)
GND: C2.2, C3.2, C6.2, C7.2, C8.2, C9.2, C10.2, C11.2, C12.2, C13.2, C14.2, Q2.1 (S), Q2.2 (S), Q2.3 (S), R3.2, R5.2, R6.2, R8.2, R20.2, U1.6 (GND), U1.8 (PLLIN), U1.12 (DRVUV), U1.25 (GND); also elsewhere on the board
unnamed: C9.1, R9.2
unnamed: R20.1, U1.11 (DRVSET)
unnamed: R6.1, U1.10 (FREQ)
unnamed: C8.1, U1.2 (SS)
PG12: R10.2, U1.9 (PGOOD); also elsewhere on the board
VIN_PROT: C2.1, C3.1, Q1.5 (D), Q3.2 (D), R2.1, R4.1, U1.19 (VIN); also elsewhere on the board

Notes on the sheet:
2 12 V / 5 A BUCK (U1 LTC7801, 148 kHz)
Peak current mode, R1 10 mΩ sense (Kelvin to SENSE+/-). RUN divider: on above 59.8 V; OVLO: off above 118.8 V.
Q3 BSP89 pre-regulates DRVCC (10 V, set by R20) from VIN until EXTVCC takes over from the 12 V output.
ITH: R9/C9 type II compensation, C10 high-frequency pole. VFB divider R7/R8: 12.0 V.
C2, C3 2.2 µF 250 V: right at Q1's drain
C13, C14 10 µF X7R 1210; C11, C12 47 µF polymer
U1 exposed pad (25) = GND: solder it, and stitch it to the ground plane with vias.

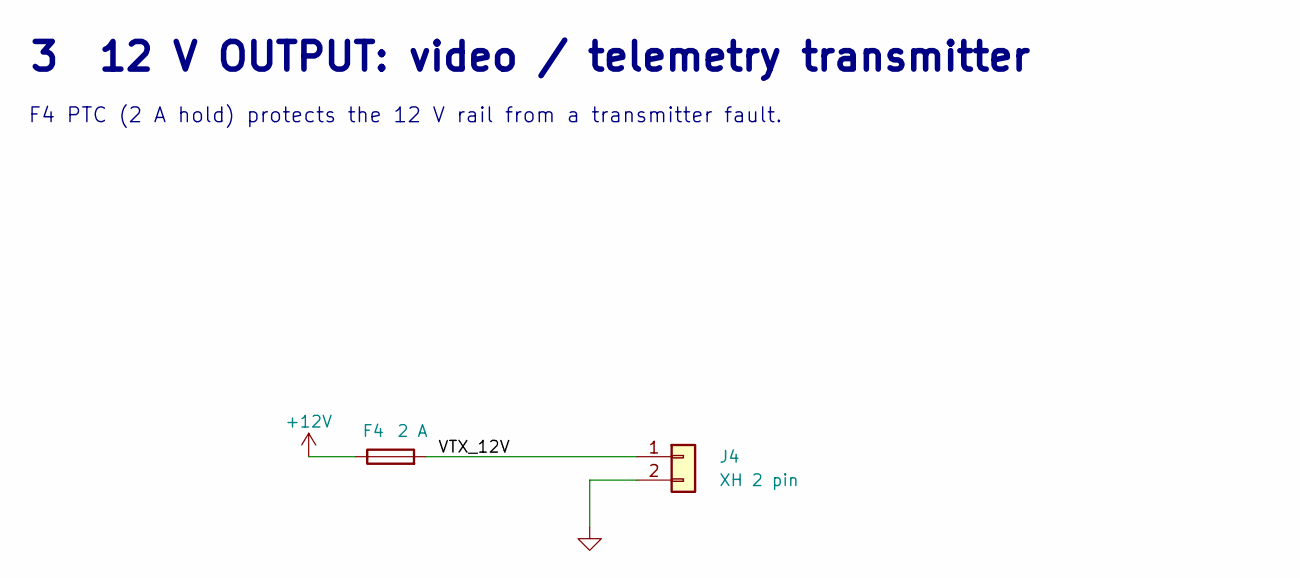
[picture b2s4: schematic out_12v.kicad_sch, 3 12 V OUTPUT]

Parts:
F4: 2 A; Fuse_1812_4532Metric; Rating 2 A hold, 16 V; MPN/Spec Bourns MF-MSMF200 (1812)
J4: XH 2 pin; JST_XH_B2B-XH-A_1x02_P2.50mm_Vertical; MPN/Spec JST XH 2 pin (3 A)

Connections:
+12V: F4.1; also elsewhere on the board
/Out_12V/VTX_12V: F4.2, J4.1
GND: J4.2; also elsewhere on the board

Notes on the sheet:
3 12 V OUTPUT: video / telemetry transmitter
F4 PTC (2 A hold) protects the 12 V rail from a transmitter fault.
